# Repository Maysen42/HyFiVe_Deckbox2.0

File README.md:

# HyFiVe - Hydrography on Fishing Vessels

<figure> 
   
</figure>

## Project Background 
Whether for modelling climate change or for our understanding of fish stocks – ocean data is essential for many disciplines. Usually, this data is collected by research vessels, which are cost-intensive and thus limited in space and time. To increase data resolution ‘vessels of opportunity’ can be a scalable alternative. In this concept vessels are used as measuring platforms, that are originally financed for a non-scientific purpose. Especially fishing vessels are of interest as they deploy gear in deep water and so make the whole water column accessible for an attached measuring system.

For this use case we developed a very flexible autonomous measuring system, which can be deployed on fishing gear to collect data in an affordable and scalable way. This was done within the **project ‘Hydrography on Fishing Vessels - HyFiVe’**
- Project period: Sept 2021 until Sept 2024
- Project partners:  
    - Thünen-Institute of Baltic Sea Fisheries (TIOF), Rostock, Germany, [https://www.thuenen.de/en/institutes/baltic-sea-fisheries/projects/fisheries-and-survey-technology/hyfive-hydrography-on-fishing-vessels](https://www.thuenen.de/en/institutes/baltic-sea-fisheries/projects/fisheries-and-survey-technology/hyfive-hydrography-on-fishing-vessels)
    - Leibnitz-Institute for Baltic Sea Research Warnemünde (IOW), Germany [https://www.io-warnemuende.de/project/278/hyfive.html](https://www.io-warnemuende.de/project/278/hyfive.html)
    - Hensel Elektronik GmbH, Rostock, Germany [https://hensel-elektronik.de](https://hensel-elektronik.de)
- Project webpage: hyfive.info
- Contact: See hyfive.info

## The HyFiVe System

This measuring system essentially consists of three components: 
- [01 Logger](./01_Logger/): Measures data with implemented OEM sensors while in the water and transmits them wireless afterwards.
- [02 Deck box](./02_Deckbox/): Receives measuring data via wifi, geo-references and stores it, visualizes it locally via webservice and transmits it to shore. The deck box also forwards config updates from server to loggers.
- [03 Land-Based Server](./03_Server/): Central infrastructure with a relational database, a configuration interface for remote maintenance and a tool for visualization of measuring data.

As overarching topic, [bi-directional communication](./bi_directional_communication/) between these components is described separately. 

The HyFiVe system offers many advantages:
- Autonomous operation up to several month
- Usable for non-experts, robust design
- Affordable price 
- Near live transmission of geo-referenced data to shore
- Scalability: Designed for a growing fleet of loggers and deck boxes
- Flexibility: Tested in various use cases, e.g. on trawl nets, as handheld probe and on sailing vessels 
- Modular design of logger facilitating easy change of sensors and integration of new ones
- Bi-directional data flow offering possibilities for remote servicing (VPN to deck box, config.json file for logger) 
- Comprehensive meta data
- Use of open sub-components and open standards lowering costs and facilitating reuse (e.g. ESP32, Raspberry Pi, nodeRed, InfluxDB, netcdf, https://cfconventions.org/ for naming variables)
- Open source, so you can modify and commercialise (according to the licenses below)

The system was developed in an agile method, so prototypes were built from an early stage on and tested continuously. Till the end of the first project in Sept 2024 the system was deployed on over ten vessels, among them research vessels, trawl fishing vessels, gill net fishing vessels and recreational vessels like sailing boats. 

<figure> 

   <figurecaption><a name="figure1">*Figure 1:*</a> *Logger, deck box and server - the three components of the HyFiVe measuring system*</figurecaption>
</figure>

## Github Repository
This documentation is aimed to enable you to build an own HyFiVe system and therefore contains detailed informations about all parts. If you are interested in building a system and lack information, please get in contact with us. 

**Disclaimer: We do not guarantee that the description is accurate throughout or complete. All your work is done at your own risk. Please comply with all necessary and legal safety precautions, especially when high voltage is involved, to avoid damage to yourself, others and the hardware.**

The three components have separate folders with hardware, software and specific information including READMEs which can be followed step by step. The READMEs contain
- Purpose and short description
- Used tools (hardware and software)
- Bills of Materials
- Additional information in the making/deploying

## Licenses
HyFiVe is an open-source project consisting of software, hardware, and documentation components. Each part of this project is licensed under a different copyleft license to ensure it remains free and open:

- Software/Code is licensed under [MPL-2.0](LICENSE_MPL-2.0)
- Hardware is licensed under [CERN-OHL-W-2.0 or later](LICENSE_CERN-OHL-W-2.0)
- Documentation is licensed under [CC-BY-SA-4.0](LICENSE_CC-BY-SA-4.0)

The HyFiVe logo is not published under above licenses and not free to use. 

An overview of the legal implications resulting from this licenses can be fund under [https://joinup.ec.europa.eu/collection/eupl/solution/joinup-licensing-assistant/jla-find-and-compare-software-licenses](https://joinup.ec.europa.eu/collection/eupl/solution/joinup-licensing-assistant/jla-find-and-compare-software-licenses).

## Funding
This project was funded by the German Federal Ministry of Food and Agriculture. 
<figure> 
   
</figure>

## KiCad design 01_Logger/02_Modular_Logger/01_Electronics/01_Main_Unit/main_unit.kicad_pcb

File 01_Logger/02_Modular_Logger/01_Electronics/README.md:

## Content

- [Logger-Mainboard (Main Unit)](#logger-mainboard-main-unit)
- [Interfaceboard (Adapter)](#interfaceboard-adapter)
- [Pinout](#pinout)
    - [Logger-Mainboard](#logger-mainboard)
    - [I2C-Adapter](#i2c-adapter)
    - [RS485-Adapter](#rs485-adapter)
    - [RS232-Adapter](#rs232-adapter)
    - [Analog-Adapter](#analog-adapter)
    - [UART-Adapter](#uart-adapter)
    - [UART Serial Port Connector for ESP32](#uart-serial-port-connector-for-esp32)
    - [JTAG Connector for Interfacebaord](#jtag-connector-for-interfacebaord)
  
---

# Logger-Mainboard (Main Unit)

1. **LED Connector**: Allows for the connection of LED indicators to provide visual status information.
2. **BMS Serial Interface**: Enables communication with the Battery Management System (BMS) for monitoring and controlling parameters.
3. **NTC Sensor Connector for Battery Charging**: Connects to an NTC sensor to monitor battery temperature during charging for safety.
4. **Wi-Fi Antenna Connector**: Attachment point for a Wi-Fi antenna to enable wireless communication.
5. **Charging Connector**: Port for connecting a power source to charge the battery.
6. **UART Serial Port Connector for ESP32**: Allows for serial communication with the ESP32 microcontroller, useful for programming and debugging.
7. **Boot BMS**: A switch to initiate the boot process for the Battery Management System.
8. **NTC Sensor Connector for BMS**: Connects to an NTC sensor for the BMS to monitor overall battery temperature.
9. **SW Push ESP32**: Enter programming/flashing mode.
10. **Reset Connector**: Connection for an external reed switch for update config file or system reset.
11. **Battery Connector**: Connection for the battery pack.
12. **Interfaceboard Connector**: I²C connection to the interfaceboards.

[Return to content](#content)

---

# Interfaceboard (Adapter)

1. **DIP-Schalter**: Used to set the bus address of the interfaceboard. This enables the board to be uniquely identified and addressed in a bus system.
2. **JTAG Connector**: Provides a connection for JTAG debugging and programming interface.
3. **Reset Button**: A button to reset the Interfaceboard.
4. **Interfaceboard Connector**: Connection to the Logger-Mainboard via I²C.
5. **Sensor Connector**: A port for connecting various types of sensors to the board for data collection.

[Return to content](#content)

---

# Pinout

### Logger-Mainboard

| Pin | J303    | J502 | J301    | J801 | J501 | BMS Serial Interface | J304    | J802      | J302             |
|-----|---------|------|---------|------|------|----------------------|---------|-----------|------------------|
| 1   | +3.3V   | TEMP | +3.3V   | GND  | VIN  | SDA                  | UART_RX | BAT PLUS  | SDA              |
| 2   | GND     | GND  | GND     | TEMP | GND  | SCL                  | +3.3V   | VC3       | SCL              |
| 3   |         |      |         |      |      | GND                  | UART_TX | VC2       | /RST             |
| 4   |         |      |         |      |      |                      | GND     | VC1       | -                |
| 5   |         |      |         |      |      |                      |         | BAT MINUS | GND              |
| 6   |         |      |         |      |      |                      |         |           | +12V             |
| 7   |         |      |         |      |      |                      |         |           | +5V              |
| 8   |         |      |         |      |      |                      |         |           | +3.3V            |

[Return to content](#content)

---

### I2C-Adapter

| Pin | X203       | X202       | X201              | X301 |
|-----|------------|------------|-------------------|------|
| 1   | VCC_TARGET | TDO/TDI    | +3.3V             | GND  |
| 2   | +3.3V      | TCK        | +5V               | +3.3V|
| 3   | VCC_TOOL   | TEST/VPP   | +12V              | -    |
| 4   |            | GND        | GND               | SCL  |
| 5   |            | VCC_TOOL   | -                 | -    |
| 6   |            | VCC_TARGET | /RST              | -    |
| 7   |            |            | SCL               | -    |
| 8   |            |            | SDA               | +12V |
| 9   |            |            |                   | +5V  |
| 10  |            |            |                   | -    |
| 11  |            |            |                   | SDA  |
| 12  |            |            |                   | -    |
| 13  |            |            |                   | -    |
| 14  |            |            |                   | -    |

[Return to content](#content)

---

### RS485-Adapter

| Pin | X203       | X202       | X201              | X301      |
|-----|------------|------------|-------------------|-----------|
| 1   | VCC_TARGET | TDO/TDI    | +3.3V             | GND       |
| 2   | +3.3V      | TCK        | +5V               | +3.3V     |
| 3   | VCC_TOOL   | TEST/VPP   | +12V              | -         |
| 4   |            | GND        | GND               | -         |
| 5   |            | VCC_TOOL   | -                 | -         |
| 6   |            | VCC_TARGET | /RST              | TX/RX LOW |
| 7   |            |            | SCL               | -         |
| 8   |            |            | SDA               | +12V      |
| 9   |            |            |                   | +5V       |
| 10  |            |            |                   | -         |
| 11  |            |            |                   | -         |
| 12  |            |            |                   | -         |
| 13  |            |            |                   | TX/RX High|
| 14  |            |            |                   | -         |

[Return to content](#content)

---

### RS232-Adapter

| Pin | X203       | X202       | X201              | X301 |
|-----|------------|------------|-------------------|------|
| 1   | VCC_TARGET | TDO/TDI    | +3.3V             | GND  |
| 2   | +3.3V      | TCK        | +5V               | +3.3V|
| 3   | VCC_TOOL   | TEST/VPP   | +12V              | TX   |
| 4   |            | GND        | GND               | -    |
| 5   |            | VCC_TOOL   | -                 | -    |
| 6   |            | VCC_TARGET | /RST              | -    |
| 7   |            |            | SCL               | -    |
| 8   |            |            | SDA               | +12V |
| 9   |            |            |                   | +5V  |
| 10  |            |            |                   | RX   |
| 11  |            |            |                   | -    |
| 12  |            |            |                   | -    |
| 13  |            |            |                   | -    |
| 14  |            |            |                   | -    |

[Return to content](#content)

---

### Analog-Adapter

| Pin | X203       | X202       | X201              | X301        |
|-----|------------|------------|-------------------|-------------|
| 1   | VCC_TARGET | TDO/TDI    | +3.3V             | GND         |
| 2   | +3.3V      | TCK        | +5V               | +3.3V       |
| 3   | VCC_TOOL   | TEST/VPP   | +12V              | -           |
| 4   |            | GND        | GND               | -           |
| 5   |            | VCC_TOOL   | -                 | -           |
| 6   |            | VCC_TARGET | /RST              | -           |
| 7   |            |            | SCL               | Analog Input|
| 8   |            |            | SDA               | +12V        |
| 9   |            |            |                   | +5V         |
| 10  |            |            |                   | -           |
| 11  |            |            |                   | -           |
| 12  |            |            |                   | -           |
| 13  |            |            |                   | -           |
| 14  |            |            |                   | -           |

[Return to content](#content)

---

### UART-Adapter

| Pin | X203       | X202       | X201              | X301    |
|-----|------------|------------|-------------------|---------|
| 1   | VCC_TARGET | TDO/TDI    | +3.3V             | GND     |
| 2   | +3.3V      | TCK        | +5V               | +3.3V   |
| 3   | VCC_TOOL   | TEST/VPP   | +12V              | -       |
| 4   |            | GND        | GND               | -       |
| 5   |            | VCC_TOOL   | -                 | TXD/TCK |
| 6   |            | VCC_TARGET | /RST              | -       |
| 7   |            |            | SCL               | -       |
| 8   |            |            | SDA               | +12V    |
| 9   |            |            |                   | +5V     |
| 10  |            |            |                   | -       |
| 11  |            |            |                   | -       |
| 12  |            |            |                   | RXD/TMS |
| 13  |            |            |                   | -       |
| 14  |            |            |                   | -       |

[Return to content](#content)

---

### UART Serial Port Connector for ESP32

[Return to content](#content)

---

### JTAG Connector for Interfacebaord

[Return to content](#content)

---

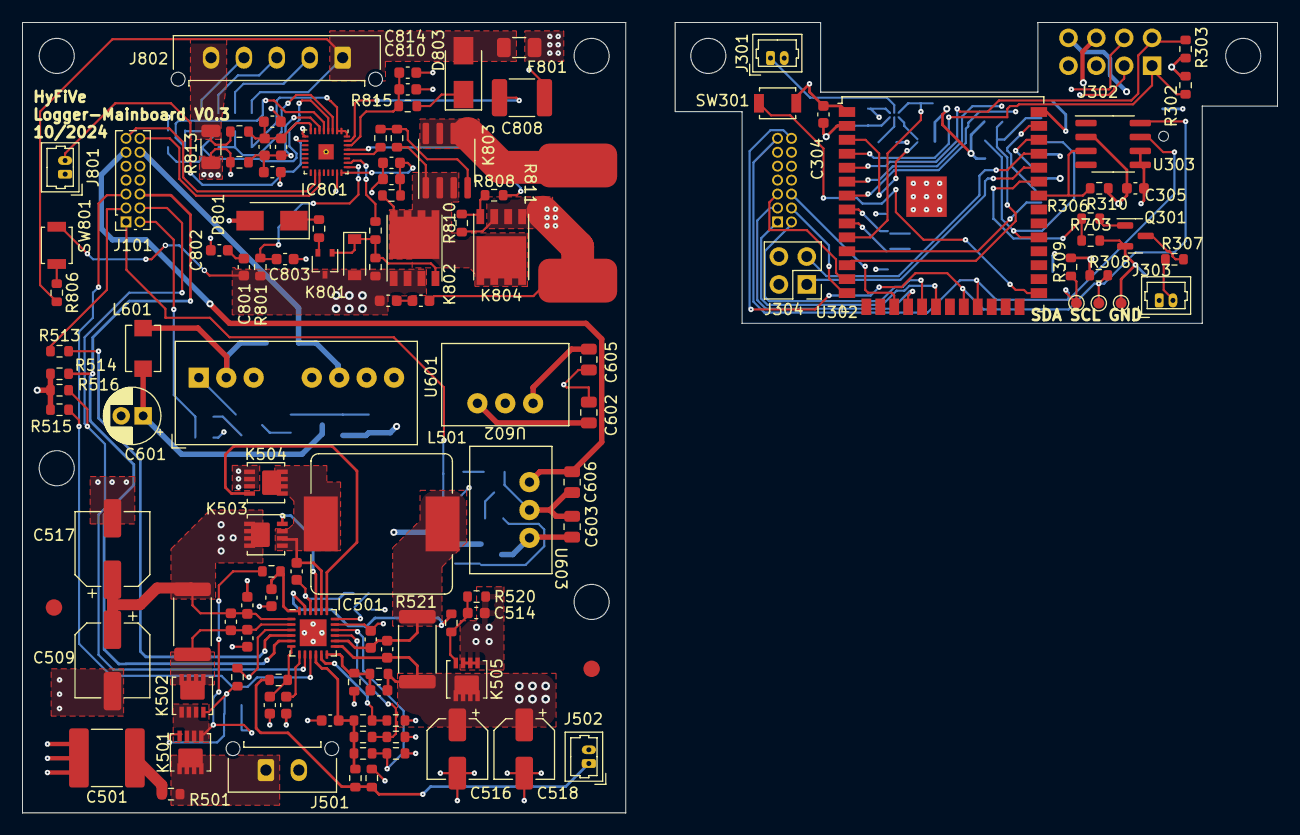
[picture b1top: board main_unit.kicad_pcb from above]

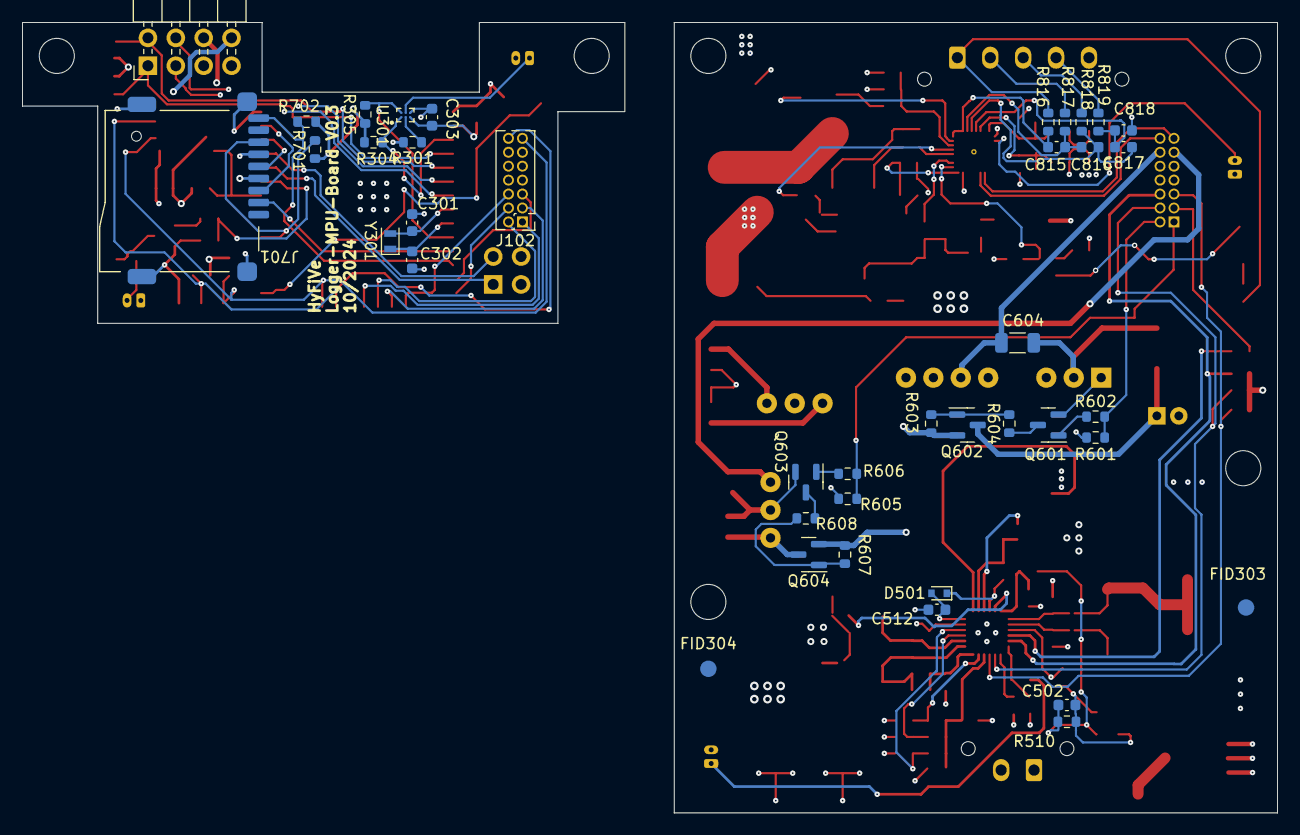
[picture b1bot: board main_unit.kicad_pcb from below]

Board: 4 copper layers, 114.4 x 72.1 mm, 167 parts (40 on the bottom side), 109 nets.

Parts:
C301, C302: 20pF; C_0603_1608Metric
C303, C304, C305, C502, C503, C505, C506, C507, C511, C513, C514, C515, C801, C802, C806, C807, C809, C812, C813, C815, C816, C817, C818: 100nF 50V; C_0603_1608Metric
C501: 47µF 35V X7R; C_2220_5650Metric
C504: 1µF 10V; C_0603_1608Metric
C508: 33nF 25V; C_0603_1608Metric
C509, C517: 47µF 35V; CP_Elec_6.3x5.4
C510, C512: 1µF 35V; C_0603_1608Metric
C516, C518: 20µF 35V; CP_Elec_5x5.3
C519: 22pF 35V; C_0603_1608Metric
C601: 10µF, 50V; CP_Radial_D5.0mm_P2.00mm
C602, C603: 22µF 30V; C_0805_2012Metric
C604: 150pF, 2kV; C_1206_3216Metric
C605, C606: 47µF 10V; C_0805_2012Metric
C803: 10nF, 50V; C_0603_1608Metric
C804, C805, C810, C814: 100pF 50V; C_0603_1608Metric
C808: 2,2µF 100V; C_1812_4532Metric
C811: 100pF 100V; C_0603_1608Metric
D501: BAT54W; D_SOD-523
D801, D803: SS1H10-E3/61T; D_SMA
D802: MMSZ5246B-7-F; D_SOD-123
F801: 12A; Fuse_1206_3216Metric
FID301, FID302, FID303, FID304: Fiducial; Passmarke
H301, H302, H303, H304, H305, H306: MountingHole; MountingHole_3.2mm_M3_ISO7380
IC501: BQ24618; VQFN-24-1EP_4x4mm_P0.5mm_EP2.45x2.45mm
IC801: BQ40Z80; RSM32 VQFN-32-1EP_4x4mm_P0.4mm_EP1.4x1.4mm_ThermalVias
J101: SFMC-107-01-L-D; PinSocket_2x07_P1.27mm_Vertical
J102: FTS-107-01-F-D; PinHeader_2x07_P1.27mm_Vertical
J301, J303: Conn_01x02; Molex_PicoBlade_53047-0210_1x02_P1.25mm_Vertical
J302: Conn_02x04_Counter_Clockwise; PinHeader_2x04_P2.54mm_Horizontal
J304: Conn_02x02_Odd_Even; PinHeader_2x02_P2.54mm_Vertical
J501: Conn_01x02; Molex_Micro-Fit_3.0_43650-0215_1x02_P3.00mm_Vertical
J502: Conn_01x02_Female; Molex_PicoBlade_53047-0210_1x02_P1.25mm_Vertical
J701: Micro_SD_Card_Det; SD_CARD_693071020811
J801: Conn_01x02_Male; Molex_PicoBlade_53047-0210_1x02_P1.25mm_Vertical
J802: Conn_01x05_Male; Molex_Micro-Fit_3.0_43650-0515_1x05_P3.00mm_Vertical
K501, K502, K505: SISH101DN-T1-GE3; PowerPAK 1212-8 Single
K503, K504: SiS412DN; PowerPAK 1212-8 Single
K801: 2N7002KW; SOT-323_SC-70
K802, K804: CSD18540Q5B; TI Q5B-Package
K803: DMP6023LSS-13; SOIC-8_3.9x4.9mm_P1.27mm
L501: 3,3µH; L_Bourns_SRP1245A
L601: 10µH; CC453232A
Q301: BSS138; SOT-23
Q601, Q603: BSS123; SOT-23
Q602, Q604: IRLML5203TRPBF; SOT-23
R301, R506, R509, R510, R520: 100k; R_0603_1608Metric
R302, R303, R304, R305, R308, R309, R310, R502, R507, R701, R702, R802, R809: 10k; R_0603_1608Metric
R306, R602, R606: 47k; R_0603_1608Metric
R307: 75; R_0603_1608Metric
R501, R511, R812, R814, R815: 100; R_0603_1608Metric
R503: 5.7k; R_0603_1608Metric
R504: R_Therm_1; R_0603_1608Metric
R505: R_Therm_2; R_0603_1608Metric
R508: 232k; R_0603_1608Metric
R512, R519, R604, R608, R808: 1k; R_0603_1608Metric
R513: 0; R_0603_1608Metric
R514, R515, R516, R523: 49,9k; R_0603_1608Metric
R517, R521: 10m; R_2512_6332Metric
R518: 10; R_0603_1608Metric
R522: 357k; R_0603_1608Metric
R601, R605: 2k7; R_0603_1608Metric
R603, R607: 680k; R_0603_1608Metric
R703: 1M; R_0603_1608Metric
R801: 1,1k; R_0603_1608Metric
R803, R807, R810: 10M; R_0603_1608Metric
R804: 4,81k; R_0603_1608Metric
R805: 510; R_0603_1608Metric
R806: 51; R_0603_1608Metric
R811: 46.4 5W; R_4527_11570Metric
R813: 1m; R_1206_3216Metric
R816, R817, R818, R819: 499; R_0603_1608Metric
SW301, SW801: SW_Push; SW_SPST_B3U-1000P
TP301, TP302, TP303: TestPoint; TestPoint_Pad_D1.0mm
U301: MAX16125WTEG00+T; WLP-6
U302: ESP32-S3-WROOM-1U
U303: DS3231MZ; SOIC-8_3.9x4.9mm_P1.27mm
U601: SPBW06F-12; Converter_DCDC_XP_POWER-ITxxxxxS_THT
U602: OKI-78SR-3.3_1.5-W36-C; DC_DC_Converter
U603: OKI-78SR-5_1.5-W36-C; DC_DC_Converter
Y301: Crystal; Crystal_SMD_TXC_9HT11-2Pin_2.0x1.2mm

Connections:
+3V3: C303.1, C304.1, C305.1, C605.1, J101.10, J102.10, J302.8, J303.1, J304.2, J701.4 (VDD), R302.1, R303.1, R304.1, R305.1, R308.1, R309.1, R310.1, R514.1, R515.1, R516.1, R701.2, R702.1, U301.C1 (VCC), U302.2 (VDD), U303.2 (VCC), U602.3 (OUT)
+5V: C606.1, J101.11, J102.11, J302.7, U603.3 (OUT)
+12V: C604.2, J101.12, J102.12, J302.6, U601.6 (+VOUT)
/MPU/Charge_Enable: J102.3, U302.18 (IO10)
/MPU/ENABLE_5V: J102.1, U302.20 (IO12)
/MPU/ENABLE_12V: J102.2, U302.19 (IO11)
/MPU/GPIO_Reserve_B2B: J302.4, U302.6 (IO6)
/MPU/I2C_BUS_CLK: J302.2, R303.2, U302.5 (IO5)
/MPU/I2C_BUS_SDA: J302.1, R302.2, U302.4 (IO4)
/MPU/I2C_SMBus_SCL: J102.14, R308.2, TP301.1, U302.22 (IO14), U303.8 (SCL)
/MPU/I2C_SMBus_SDA: J102.13, R309.2, TP302.1, U302.23 (IO21), U303.7 (SDA)
/MPU/Interface_RST: J302.3, U302.7 (IO7)
/MPU/LED_STATUS: R306.1, R703.1, U302.35 (IO42)
/MPU/RST: R304.2, U301.A1 (/RESET), U302.3 (EN)
/MPU/RTC_INTERRUPT: R310.2, U302.34 (IO41), U303.3 (~INT/SQW)
/MPU/SD_CARD_DETECT: J701.9 (DET_B), R702.2, U302.12 (IO8)
/MPU/SD_V_SPI_CLK: J701.5 (CLK), U302.38 (IO2)
/MPU/SD_V_SPI_CS: J701.2 (DAT3/CD), U302.11 (IO18)
/MPU/SD_V_SPI_MISO: J701.7 (DAT0), R701.1, U302.31 (IO38)
/MPU/SD_V_SPI_MOSI: J701.3 (CMD), U302.39 (IO1)
/MPU/UART_RXD0: J304.1, U302.36 (RXD0)
/MPU/UART_TXD0: J304.3, U302.37 (TXD0)
/MPU/~PG: J102.4, U302.14 (IO20)
/MPU/~STAT1: J102.6, U302.17 (IO9)
/MPU/~STAT2: J102.5, U302.13 (IO19)
/power/BMS/BAT_MINUS: J802.5, R813.2, R814.1
/power/BMS/BAT_PLUS: D803.2 (A), F801.2, J802.1, R806.2, R816.1
/power/BMS/BAT_PLUS_F: C807.1, F801.1, K804.1, K804.2, K804.3, R810.2, R811.2
/power/BMS/PACK+: C515.1, C516.1, C518.1, C519.2, C801.1, C806.1, D802.2 (A), IC501.13 (SRN), K505.5, K505.6, K505.7, K505.8, K505.9, K801.3, K802.1, K802.2, K802.3, R521.1, R522.1, R801.2, R803.2, SW801.2
/power/Battery_Charger/ACP: C503.2, C505.1, IC501.2 (ACP), K502.5, K502.6, K502.7, K502.8, K502.9, R517.2
/power/Battery_Charger/Thermistor: J502.1, R504.1, R505.2, R511.1
/power/Battery_Charger/VIN: J501.1, K501.5, K501.6, K501.7, K501.8, K501.9, R501.1
/power/Battery_Charger/VREF: C504.1, IC501.10 (VREF), R502.1, R504.2, R506.1, R508.1
/power/Charge_Enable: J101.3, R513.1
/power/ENABLE_5V: J101.1, R605.2, R606.1
/power/ENABLE_12V: J101.2, R601.2, R602.1
/power/I2C_SMBus_SCL: IC801.19 (SMBC), J101.14
/power/I2C_SMBus_SDA: IC801.18 (SMBD), J101.13
/power/System+: C505.2, C507.2, C509.1, C514.1, C517.1, C602.1, IC501.1 (ACN), K503.5, K503.6, K503.7, K503.8, K503.9, K505.1, K505.2 (S), K505.3 (S), Q602.2 (S), Q604.2 (S), R517.1, R520.1, R603.2, R607.2, U602.1 (IN)
/power/~PG: IC501.8 (~PG), J101.4, R516.2
/power/~STAT1: IC501.5 (~STAT1), J101.6, R514.2
/power/~STAT2: IC501.9 (~STAT2), J101.5, R515.2
GND: C301.2, C302.2, C303.2, C304.2, C305.2, C501.2, C503.1, C504.2, C506.1, C507.1, C508.1, C509.2, C510.2, C512.2, C513.1, C516.2, C517.2, C518.2, C601.2, C602.2, C603.2, C605.2, C606.2, C802.2, C803.2, C804.1, C805.1, C808.2, C809.1, C810.1, C813.1, C814.1, C818.2, D801.2 (A), IC501.17 (GND), IC501.25 (PwrPad), IC801.9 (VSS), IC801.23 (FUSE), IC801.33 (PAD), J101.7, J101.8, J102.7, J102.8, J301.2, J302.5, J304.4, J501.2, J502.2, J701.6 (VSS), J701.10 (DET_A), J701.11 (SHIELD), J701.12 (SHIELD), J701.13 (SHIELD), J801.1, K504.1, K504.2 (S), K504.3 (S), Q301.2 (S), Q601.2 (S), Q603.2 (S), R301.2, R503.2, R505.1, R507.2, R509.2, R523.2, R601.1, R605.1, R703.2, R812.2, R813.1, SW301.2, TP303.1, U301.C2 (GND), U302.1 (GND), U302.40 (GND), U302.EPAD (GND), U303.5 (GND), U303.6 (VBAT), U601.1 (-VIN), U601.7 (-VOUT), U602.2 (GND), U603.2 (GND)
unnamed: C501.1, R501.2
unnamed: C502.1, K501.1, K501.2 (S), K501.3 (S), K502.1, K502.2 (S), K502.3 (S), R510.1, R518.2
unnamed: C502.2, K501.4, K502.4, R510.2, R512.1
unnamed: C514.2, K505.4, R519.1, R520.2
unnamed: C801.2, C802.1
unnamed: C806.2, C807.2
unnamed: C512.1, D501.2 (A), IC501.18 (REGN)
unnamed: C511.1, D501.1 (K), IC501.22 (BTST)
unnamed: D801.1 (K), R802.1
unnamed: D802.1 (K), K801.1, K802.4, R803.1, R804.2
unnamed: D803.1 (K), R815.1
unnamed: IC501.16 (ACSET), R502.2, R503.1
unnamed: IC501.4 (CE), R513.2
unnamed: IC501.21 (HIDRV), K503.4
unnamed: IC501.11 (ISET1), R508.2, R509.1
unnamed: IC501.15 (ISET2), R506.2, R507.1
unnamed: IC501.19 (LODRV), K504.4
unnamed: C511.2, IC501.20 (PH), K503.1, K503.2 (S), K503.3 (S), K504.5, K504.6, K504.7, K504.8, K504.9, L501.1
unnamed: C513.2, C515.2, IC501.14 (SRP), L501.2, R521.2
unnamed: C506.2, IC501.6 (TS), R511.2
unnamed: C508.2, IC501.7 (TTC)
unnamed: C510.1, IC501.24 (VCC), R518.1
unnamed: C519.1, IC501.12 (VFB), R522.2, R523.1
unnamed: IC501.3 (~ACDRV), R512.2
unnamed: IC501.23 (~BATDRV), R519.2
unnamed: C810.2, C814.2, IC801.30 (BAT), R815.2
unnamed: IC801.29 (CHG), R808.1
unnamed: IC801.26 (DSG), R804.1
unnamed: C808.1, IC801.31 (PBI)
unnamed: IC801.28 (PCHG), R809.1
unnamed: C803.1, IC801.25 (Pack), R801.1
unnamed: C809.2, C811.2, C812.2, IC801.6 (SRN), R812.1
unnamed: C811.1, C812.1, C813.2, IC801.8 (SRP), R814.2
unnamed: IC801.10 (TS1), J801.2
unnamed: C817.2, C818.1, IC801.5 (VC1), R819.2
unnamed: C816.2, C817.1, IC801.4 (VC2), R818.2
unnamed: C815.2, C816.1, IC801.3 (VC3), R817.2
unnamed: C815.1, IC801.1 (VC5), IC801.2 (VC4), IC801.32 (VC6), R816.2
unnamed: C804.2, C805.2, IC801.24 (VCC), R805.1
unnamed: J301.1, U301.B2 (/MR)
unnamed: J303.2, R307.1
unnamed: J802.2, R817.1
unnamed: J802.3, R818.1
unnamed: J802.4, R819.1
unnamed: K801.2, R802.2
unnamed: K802.5, K802.6, K802.7, K802.8, K802.9, K803.1, K803.2, K803.3, K804.5, K804.6, K804.7, K804.8, K804.9, R805.2, R807.2
unnamed: K803.4, R807.1, R809.2
unnamed: K803.5, K803.6, K803.7, K803.8, R811.1
unnamed: K804.4, R808.2, R810.1
unnamed: Q301.3 (D), R307.2
unnamed: Q301.1 (G), R306.2
unnamed: Q601.3 (D), R604.1
unnamed: Q601.1 (G), R602.2
unnamed: C601.1, L601.1, Q602.3 (D)
unnamed: Q602.1 (G), R603.1, R604.2
unnamed: Q603.3 (D), R608.1
unnamed: Q603.1 (G), R606.2
unnamed: C603.1, Q604.3 (D), U603.1 (IN)
unnamed: Q604.1 (G), R607.1, R608.2
unnamed: R806.1, SW801.1
unnamed: R301.1, U301.B1 (SEL)
unnamed: R305.2, U301.A2 (/SRESET), U302.10 (IO17)
unnamed: SW301.1, U302.27 (IO0)
unnamed: C301.1, U302.8 (IO15), Y301.2
unnamed: C302.1, U302.9 (IO16), Y301.1
unnamed: C604.1, L601.2, U601.2 (+VIN)

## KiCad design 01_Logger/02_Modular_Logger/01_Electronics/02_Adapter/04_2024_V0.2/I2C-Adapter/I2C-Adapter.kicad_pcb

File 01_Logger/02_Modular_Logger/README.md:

# Assembly Instructions

## 1. Battery and Wi-Fi Antenna

1. Place the battery into the battery holder.
2. Attach the Wi-Fi antenna.

<table>
  <tr>
    <td></td>
    <td></td>
    <td></td>
    <td></td>
  </tr>
</table>

## 2. Measurement Sensors

Attach the measurement sensors.

## 3. Mainboard and Interface Board

1. Connect the mainboard to the interface board.
2. Ensure the correct polarity of the connector.

<table>
  <tr>
    <td></td>
    <td></td>
    <td></td>
  </tr>
</table>

## 4. Screw Components and Connect Plugs

1. Screw the parts together.
2. Plug in both NTC connectors.
3. Plug in the LED and reed switch connectors.
4. Connect the charging plug.

<table>
  <tr>
    <td></td>
    <td></td>
    <td></td>
  </tr>
</table>

## 5. LED and Reed Switch

1. Attach the LED and reed switch.
2. Secure them with hot glue.

## 6. Configure SD Card

Configure the SD card with the file `loggerConfig/logger_XX_config_2024XXXXXXXX.json`. Pay attention to the following points:

1. **Filename**: 
   - Replace "XX" in the filename with the correct logger number and date in the format year/month/day/hour/minute.
   - Example: For logger 13, the filename would be `logger_13_config_202409131028.json`

2. **Logger ID**:
   - In the configuration file, the "logger_id" field must contain the correct logger number.
   - Example: `"logger_id": "13"`

3. **Wi-Fi Setup**:
   - Configure the Wi-Fi settings.
   - The first Wi-Fi login should be for the corresponding deck box.
   - You can configure up to 5 different Wi-Fi networks.

Example for Wi-Fi configuration:

```json
"wifi": [
  {
    "ssid": "Deckbox_SSID",
    "password": "Deckbox_Password"
  },
  {
    "ssid": "Second_WiFi",
    "password": "Second_Password"
  }
]
```

## 7. Connect Battery and Start Device

1. Connect the battery voltage to the mainboard.
2. Press the Boot-BMS button.
3. The board starts and can be assembled.
4. Leak test still needs to be carried out

<table>
  <tr>
    <td></td>
    <td></td>
    <td></td>
  </tr>
</table>

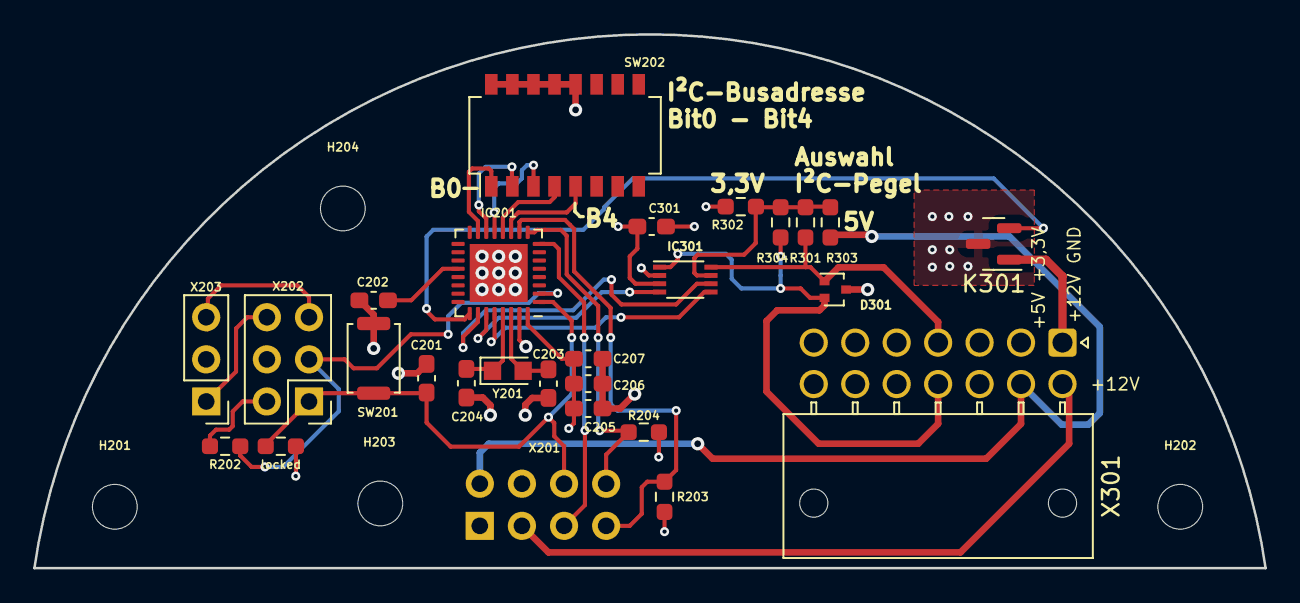
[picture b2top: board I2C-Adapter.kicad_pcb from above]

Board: 4 copper layers, 74.2 x 32.2 mm, 31 parts (1 on the bottom side), 28 nets.

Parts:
C201: 1nF; C_0603_1608Metric_Pad1.08x0.95mm_HandSolder
C202: 1µF, <200m ESR; C_0603_1608Metric_Pad1.08x0.95mm_HandSolder
C203, C204: 20pF; C_0603_1608Metric_Pad1.08x0.95mm_HandSolder
C205, C301: 100nF; C_0603_1608Metric_Pad1.08x0.95mm_HandSolder
C206: 1µF; C_0603_1608Metric_Pad1.08x0.95mm_HandSolder
C207: 4,7µF; C_0603_1608Metric_Pad1.08x0.95mm_HandSolder
D301: RCLAMP0582B; SOT-416
H201, H202, H203, H204: MountingHole; MountingHole_2.7mm_M2.5
IC201: MSP430FR2673; VQFN-32-1EP_5x5mm_P0.5mm_EP3.5x3.5mm
IC301: TXS0102DCU; VSSOP-8_2.3x2mm_P0.5mm
K301: SSM3K127TU; SOT-23
R202: 330; R_0603_1608Metric_Pad0.98x0.95mm_HandSolder
R203, R204: 10k NB; R_0603_1608Metric_Pad0.98x0.95mm_HandSolder
R301, R304: 10k n.b.; R_0603_1608Metric_Pad0.98x0.95mm_HandSolder
R302: 0R; R_0603_1608Metric_Pad0.98x0.95mm_HandSolder
R303: 0R n.b.; R_0603_1608Metric_Pad0.98x0.95mm_HandSolder
SW201: SKRKAEE020; SW_Push_SPST_NO_Alps_SKRK
SW202: A6H-8101; SW_DIP_SPSTx08_Slide_Omron_A6H-8101_W6.15mm_P1.27mm
X201: ESQ-104-14-G-D; PinSocket_2x04_P2.54mm_Vertical
X202: Conn_02x03_Counter_Clockwise; PinHeader_2x03_P2.54mm_Vertical
X203: Conn_01x03; PinHeader_1x03_P2.54mm_Vertical
X301: Molex Nano-Fit 103514-1*114; Molex_Nano-Fit_105314-xx14_2x07_P2.50mm_Horizontal
Y201: 9HT11-32.768KDZF-T; Crystal_SMD_TXC_9HT11-2Pin_2.0x1.2mm_HandSoldering
locked: 47k; R_0603_1608Metric_Pad0.98x0.95mm_HandSolder

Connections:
+3V3: C205.1, C206.1, C207.1, C301.1, IC201.32 (DVCC), IC301.3 (VCCA), R203.2, R204.2, R302.1, X201.1, X203.2, X301.2, locked.1
+5V: R303.1, X201.2, X301.9
+12V: X201.3, X301.8
/MCU/ADDR_B0: IC201.15 (P3.4/TA2CLK/COMP0OUT/CAP0.3), SW202.1
/MCU/ADDR_B1: IC201.14 (P2.3/TA2.0/CAP0.2), SW202.2
/MCU/ADDR_B2: IC201.13 (P3.3/TA2.1/CAP0.1), SW202.3
/MCU/ADDR_B3: IC201.12 (P3.0/TA2.2/CAP0.0), SW202.4
/MCU/ADDR_B4: IC201.11 (P2.2/SYNC/ACLK/COMP0.1), SW202.5
/MCU/GPIO_Reserve_B2B: IC201.8 (P1.1/UCB0CLK/TA0.1/COMP0.0/A1), X201.5
/MCU/Interface_Enable: IC201.26 (P3.5/UCB1CLK/TB0TRG/CAP3.1), IC301.6 (OE)
/MCU/Sensor_Lowside_Switch: IC201.25 (P2.7/UCB1STE/CAP3.0), K301.2
/MCU/TEST_SBWTCK: IC201.2 (TEST/SBWTCK), R202.2, X202.3
/MCU/UCB0_SCL: IC201.10 (P1.3/UCB0SOMI/UCB0SCL/MCLK/A3), R203.1, X201.7
/MCU/UCB0_SDA: IC201.9 (P1.2/UCB0SIMO/UCB0SDA/TA0.2/A2/Veref-), R204.1, X201.8
/MCU/UCB1_SCL: IC201.28 (P3.6/UCB1SOMI/UCB1SCL/CAP3.3), IC301.5 (A1)
/MCU/UCB1_SDA: IC201.27 (P3.2/UCB1SIMO/UCB1SDA/CAP3.2), IC301.4 (A2)
/MCU/VCC_TARGET: X202.6, X203.1
/MCU/VCC_TOOL: X202.5, X203.3
/MCU/XIN: C203.1, IC201.30 (P2.1/XIN), Y201.2
/MCU/XOUT: C204.1, IC201.29 (P2.0/XOUT), Y201.1
/MCU/~RST/SBWTDIO: C201.1, IC201.1 (~RST/NMI/SBWTDIO), SW201.2, X201.6, X202.1, locked.2
GND: C201.2, C202.2, C203.2, C204.2, C205.2, C206.2, C207.2, C301.2, D301.3 (A), IC201.31 (DVSS), IC201.33 (PAD), IC301.2 (GND), K301.3, SW201.1, SW202.12, SW202.13, SW202.14, SW202.15, SW202.16, X201.4, X202.4
unnamed: C202.1, IC201.20 (VREG)
unnamed: D301.1 (K1), IC301.8 (B1), R301.2, X301.4
unnamed: D301.2 (K2), IC301.1 (B2), R304.2, X301.11
unnamed: IC301.7 (VCCB), R301.1, R302.2, R303.2, R304.1
unnamed: R202.1, X202.2
unnamed: K301.1, X301.1

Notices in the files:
01_Logger/02_Modular_Logger/03_Software/Interfaceboard/main.c:
CopyrightText: (C) 2024 Hensel Elektronik GmbH
parts and their libraries:
Copyright 2021 Accelerated Designs. All rights reserved.
